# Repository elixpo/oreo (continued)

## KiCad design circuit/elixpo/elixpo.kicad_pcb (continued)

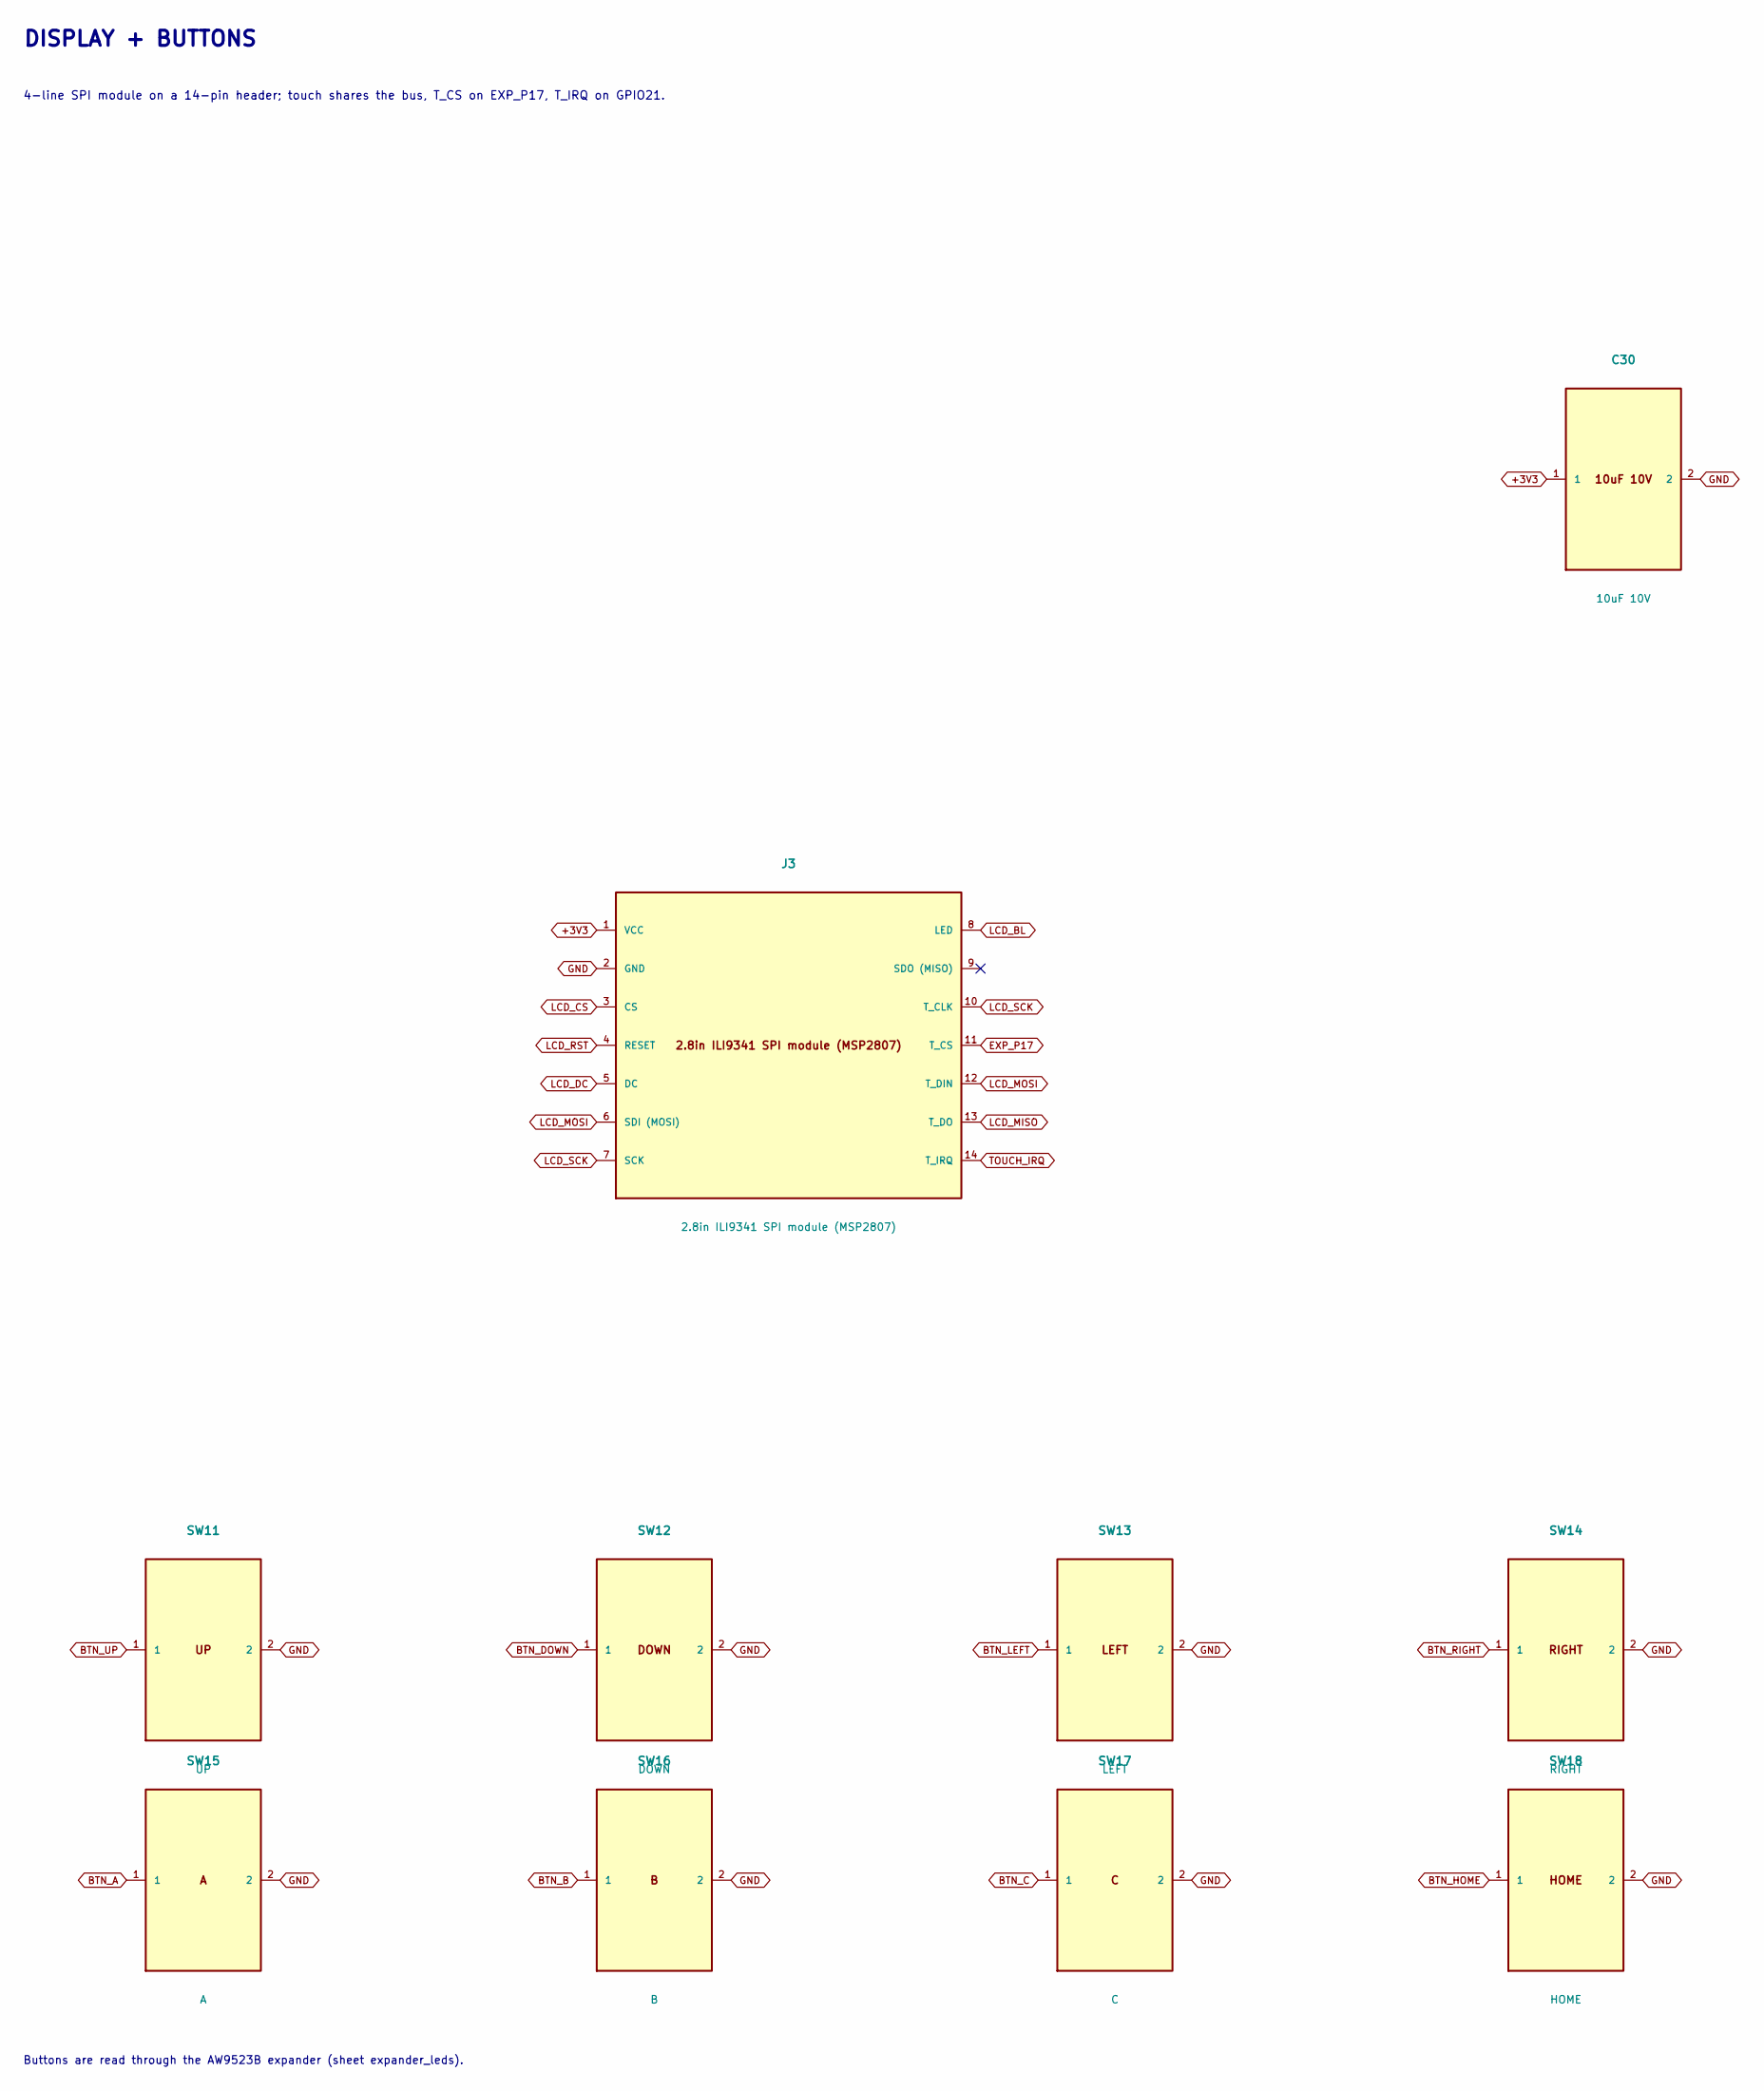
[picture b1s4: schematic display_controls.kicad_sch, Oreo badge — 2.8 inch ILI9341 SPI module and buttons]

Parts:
C30: 10uF 10V; C_0805_2012Metric
J3: 2.8in ILI9341 SPI module (MSP2807); PinSocket_1x14_P2.54mm_Vertical
SW11: UP; SW_PUSH_6mm
SW12: DOWN; SW_PUSH_6mm
SW13: LEFT; SW_PUSH_6mm
SW14: RIGHT; SW_PUSH_6mm
SW15: A; SW_PUSH_6mm
SW16: B; SW_PUSH_6mm
SW17: C; SW_PUSH_6mm
SW18: HOME; SW_PUSH_6mm

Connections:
BTN_A: SW15.1; also elsewhere on the board
BTN_B: SW16.1; also elsewhere on the board
BTN_C: SW17.1; also elsewhere on the board
BTN_DOWN: SW12.1; also elsewhere on the board
BTN_HOME: SW18.1; also elsewhere on the board
BTN_LEFT: SW13.1; also elsewhere on the board
BTN_RIGHT: SW14.1; also elsewhere on the board
BTN_UP: SW11.1; also elsewhere on the board
EXP_P17: J3.11 (T_CS); also elsewhere on the board
GND: C30.2, J3.2 (GND), SW11.2, SW12.2, SW13.2, SW14.2, SW15.2, SW16.2, SW17.2, SW18.2; also elsewhere on the board
LCD_5V: C30.1, J3.1 (VCC); also elsewhere on the board
LCD_BL: J3.8 (LED); also elsewhere on the board
LCD_CS: J3.3 (CS); also elsewhere on the board
LCD_DC: J3.5 (DC); also elsewhere on the board
LCD_MISO: J3.13 (T_DO); also elsewhere on the board
LCD_MOSI: J3.6 (SDI (MOSI)), J3.12 (T_DIN); also elsewhere on the board
LCD_RST: J3.4 (RESET); also elsewhere on the board
LCD_SCK: J3.7 (SCK), J3.10 (T_CLK); also elsewhere on the board
TOUCH_IRQ: J3.14 (T_IRQ); also elsewhere on the board

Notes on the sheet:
DISPLAY + BUTTONS
4-line SPI module on a 14-pin header; touch shares the bus, T_CS on EXP_P17, T_IRQ on GPIO21.
Buttons are read through the AW9523B expander (sheet expander_leds).

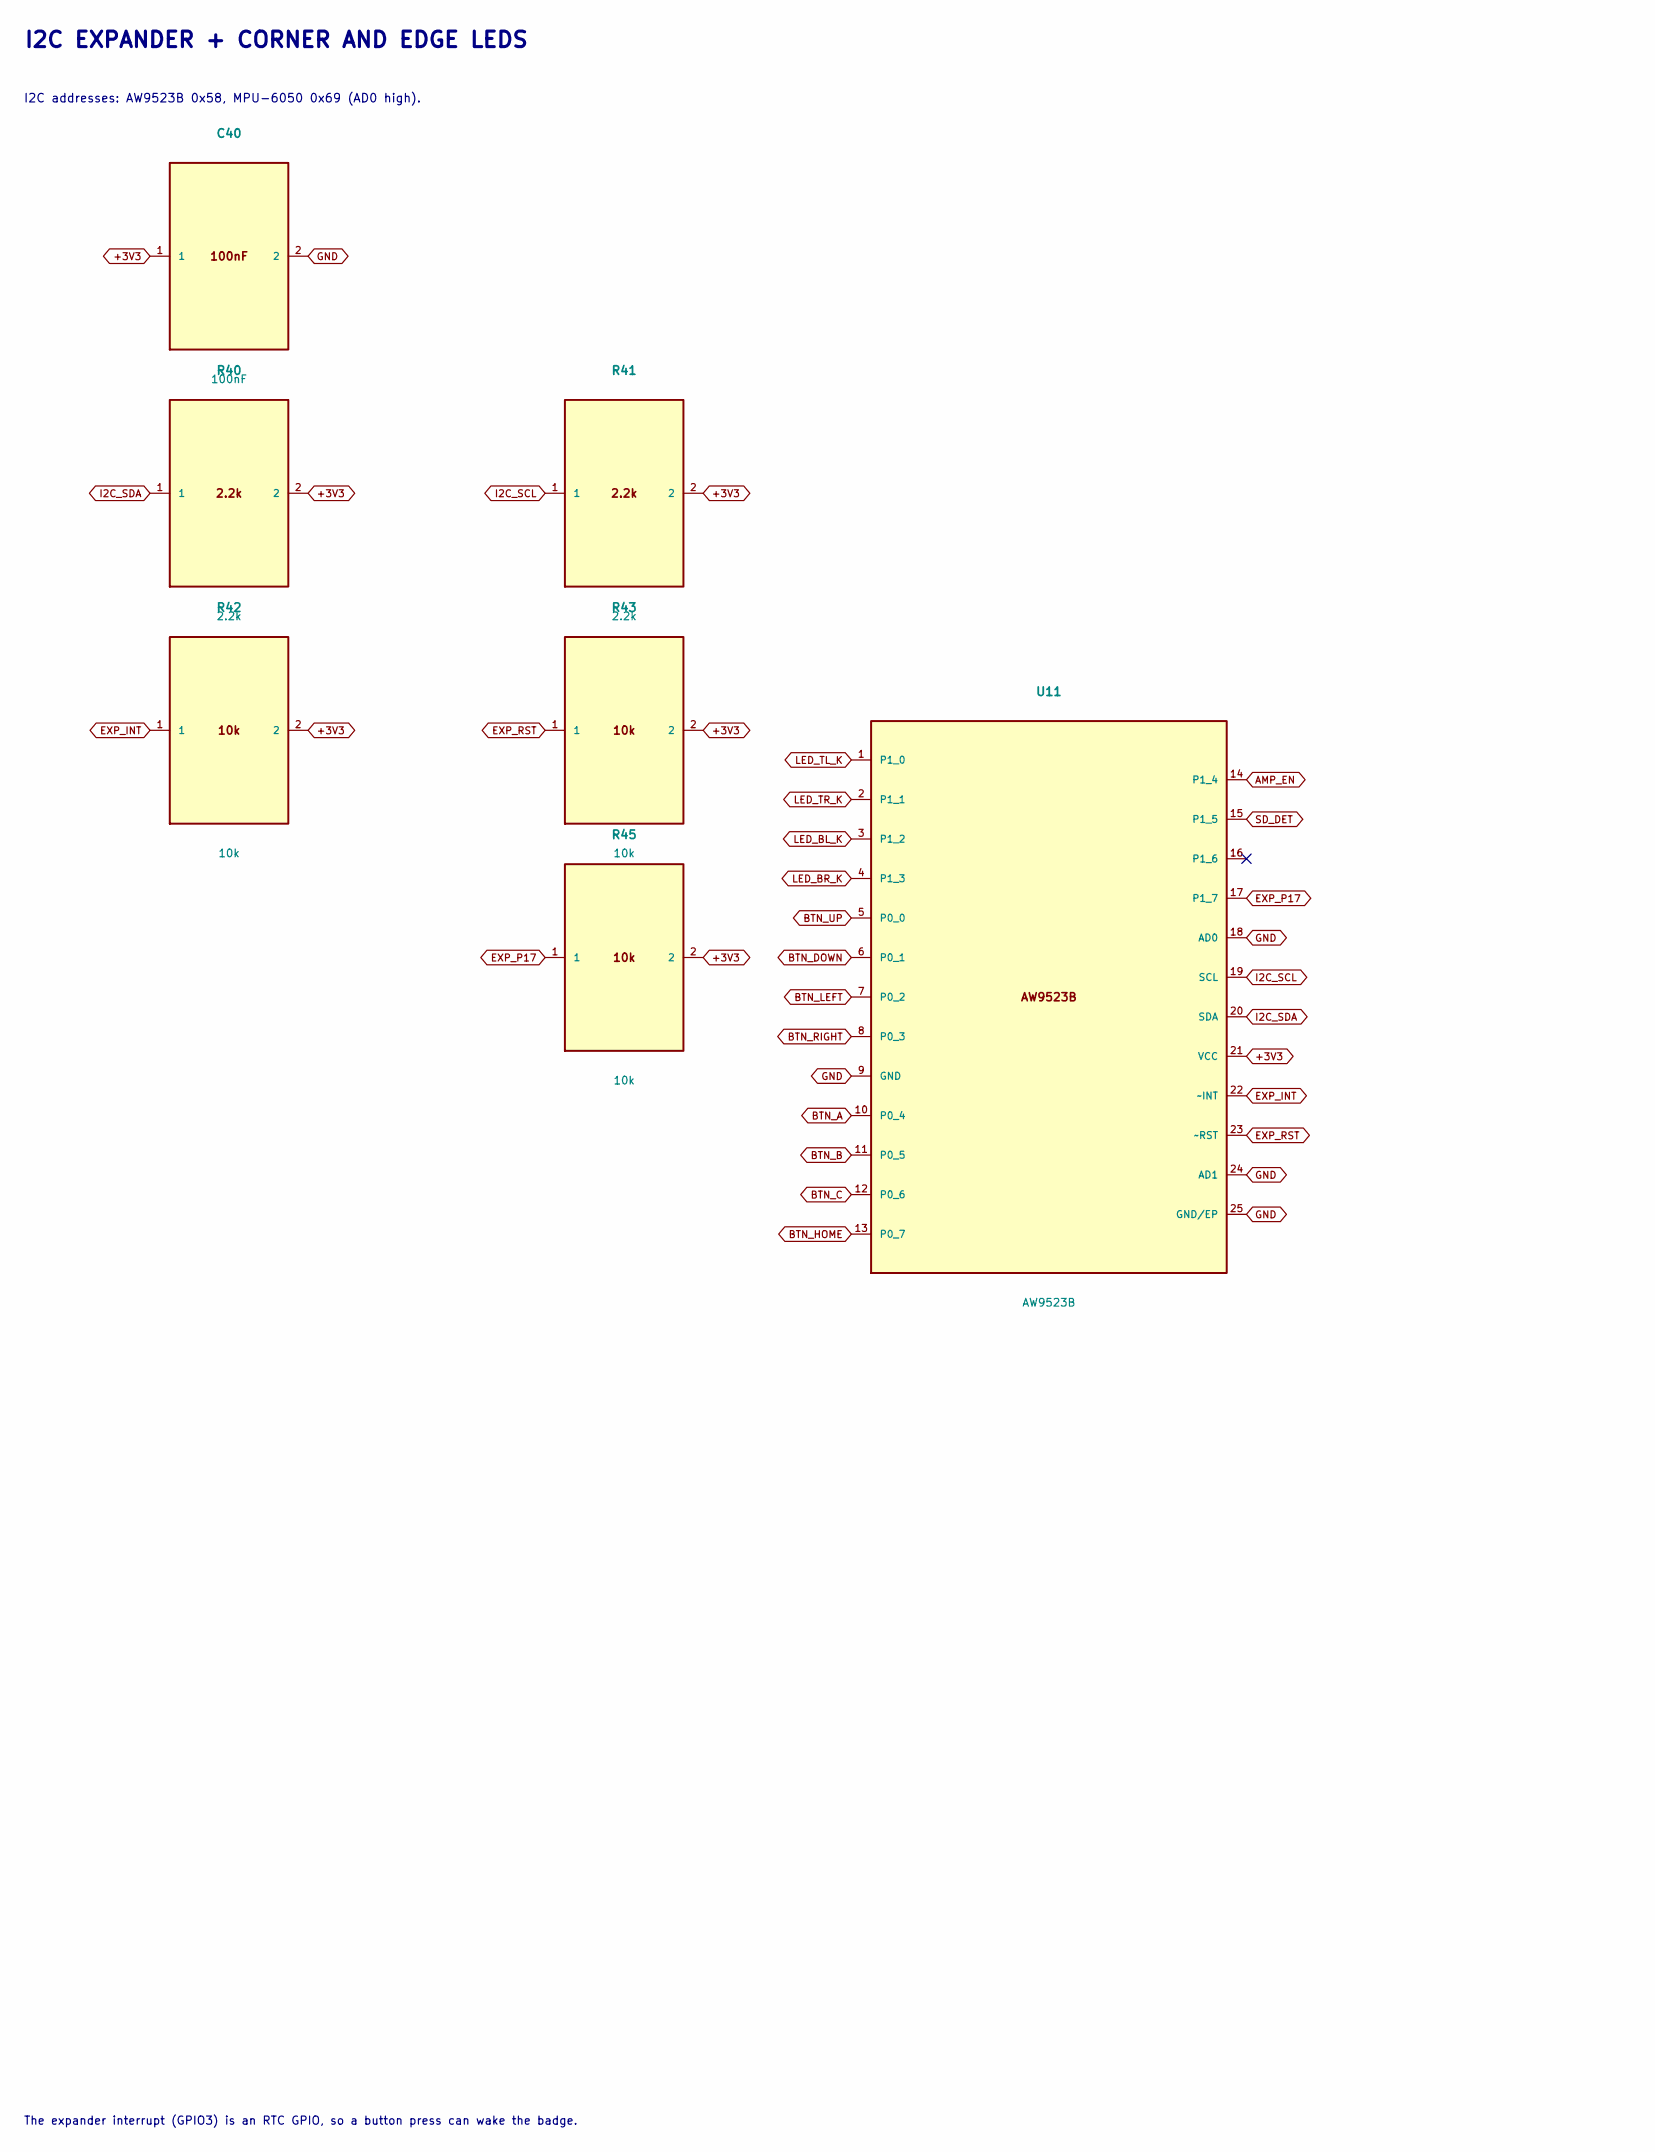
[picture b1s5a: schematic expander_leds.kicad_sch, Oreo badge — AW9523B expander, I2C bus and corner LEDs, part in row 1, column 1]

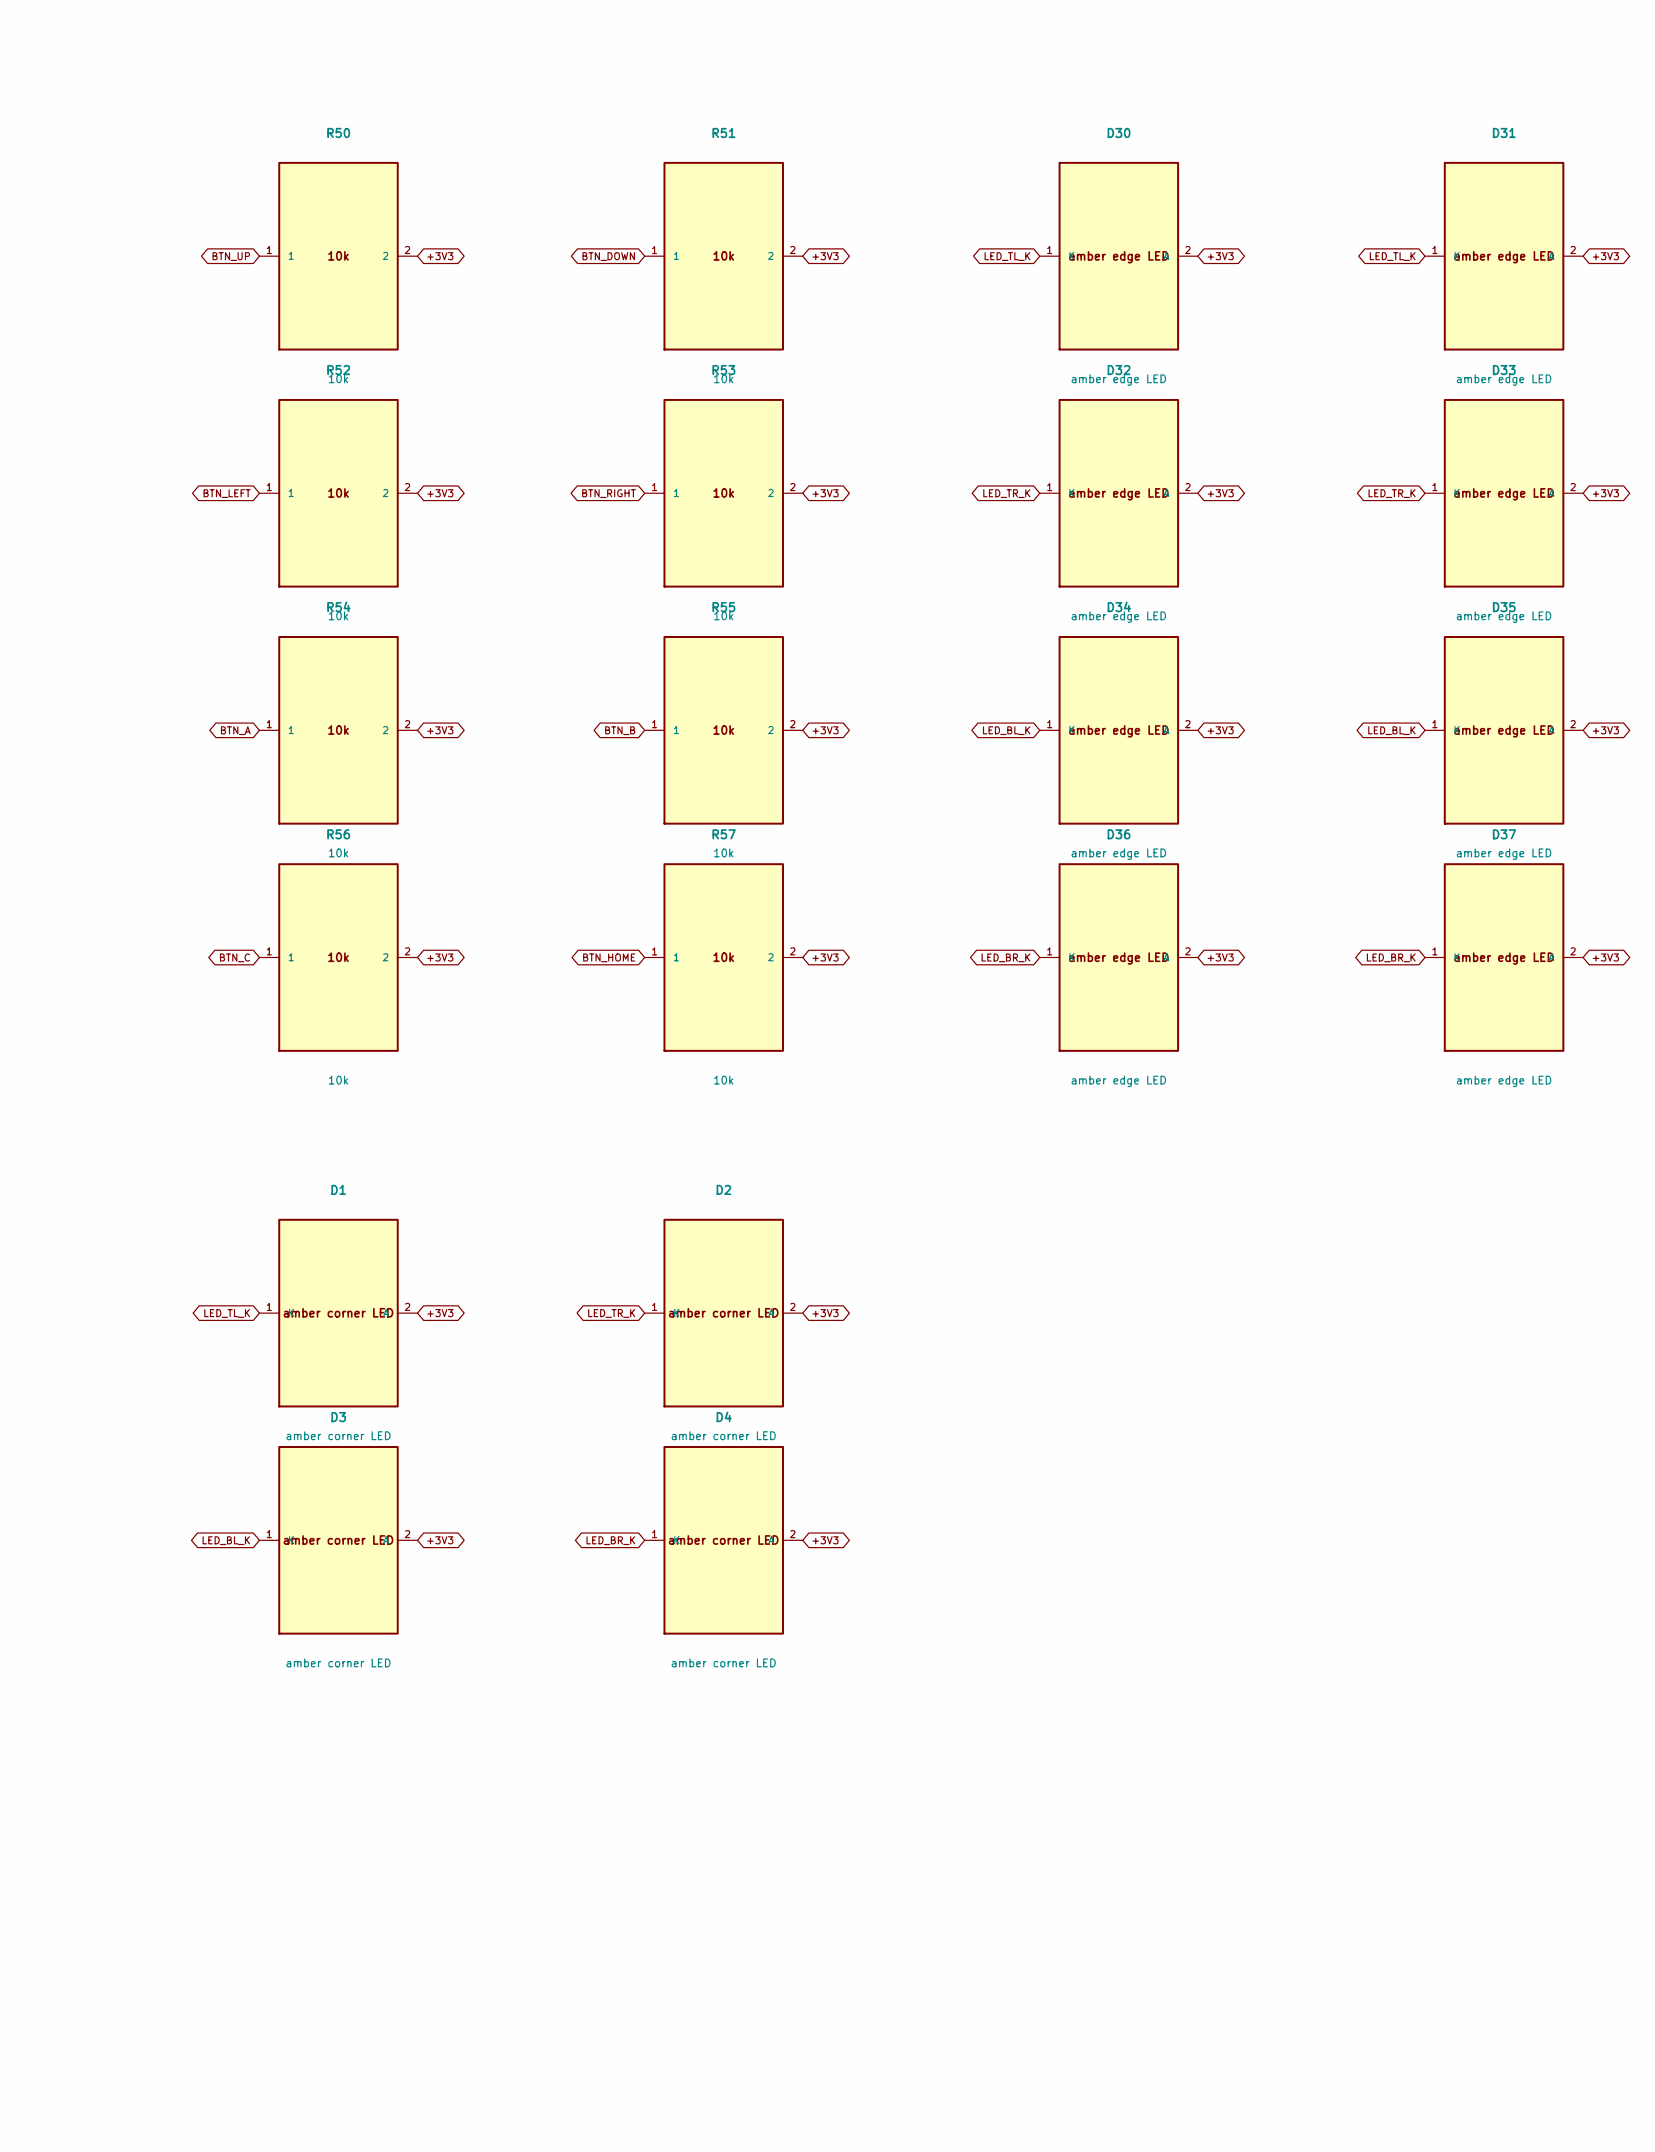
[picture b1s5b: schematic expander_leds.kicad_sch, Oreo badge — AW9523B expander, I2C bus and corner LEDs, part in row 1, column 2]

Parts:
C40: 100nF; C_0402_1005Metric
D1, D2, D3, D4: amber corner LED; LED_0603_1608Metric
D30, D31, D32, D33, D34, D35, D36, D37: amber edge LED; LED_0603_1608Metric
R40, R41: 2.2k; R_0402_1005Metric
R42, R43, R45, R50, R51, R52, R53, R54, R55, R56, R57: 10k; R_0402_1005Metric
U11: AW9523B; QFN-24-1EP_4x4mm_P0.5mm_EP2.7x2.7mm

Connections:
AMP_EN: U11.14 (P1_4); also elsewhere on the board
AUX_ON_N: U11.16 (P1_6); also elsewhere on the board
BTN_A: R54.1, U11.10 (P0_4); also elsewhere on the board
BTN_B: R55.1, U11.11 (P0_5); also elsewhere on the board
BTN_C: R56.1, U11.12 (P0_6); also elsewhere on the board
BTN_DOWN: R51.1, U11.6 (P0_1); also elsewhere on the board
BTN_HOME: R57.1, U11.13 (P0_7); also elsewhere on the board
BTN_LEFT: R52.1, U11.7 (P0_2); also elsewhere on the board
BTN_RIGHT: R53.1, U11.8 (P0_3); also elsewhere on the board
BTN_UP: R50.1, U11.5 (P0_0); also elsewhere on the board
EXP_INT: R42.1, U11.22 (~INT); also elsewhere on the board
EXP_P17: R45.1, U11.17 (P1_7); also elsewhere on the board
EXP_RST: R43.1, U11.23 (~RST)
GND: C40.2, U11.9 (GND), U11.18 (AD0), U11.24 (AD1), U11.25 (GND/EP); also elsewhere on the board
I2C_SCL: R41.1, U11.19 (SCL); also elsewhere on the board
I2C_SDA: R40.1, U11.20 (SDA); also elsewhere on the board
LED_BL_K: D3.1 (K), D34.1 (K), D35.1 (K), U11.3 (P1_2)
LED_BR_K: D4.1 (K), D36.1 (K), D37.1 (K), U11.4 (P1_3)
LED_TL_K: D1.1 (K), D30.1 (K), D31.1 (K), U11.1 (P1_0)
LED_TR_K: D2.1 (K), D32.1 (K), D33.1 (K), U11.2 (P1_1)
SD_DET: U11.15 (P1_5); also elsewhere on the board

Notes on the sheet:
I2C EXPANDER + CORNER AND EDGE LEDS
I2C addresses: AW9523B 0x58, MPU-6050 0x69 (AD0 high).
The expander interrupt (GPIO3) is an RTC GPIO, so a button press can wake the badge.

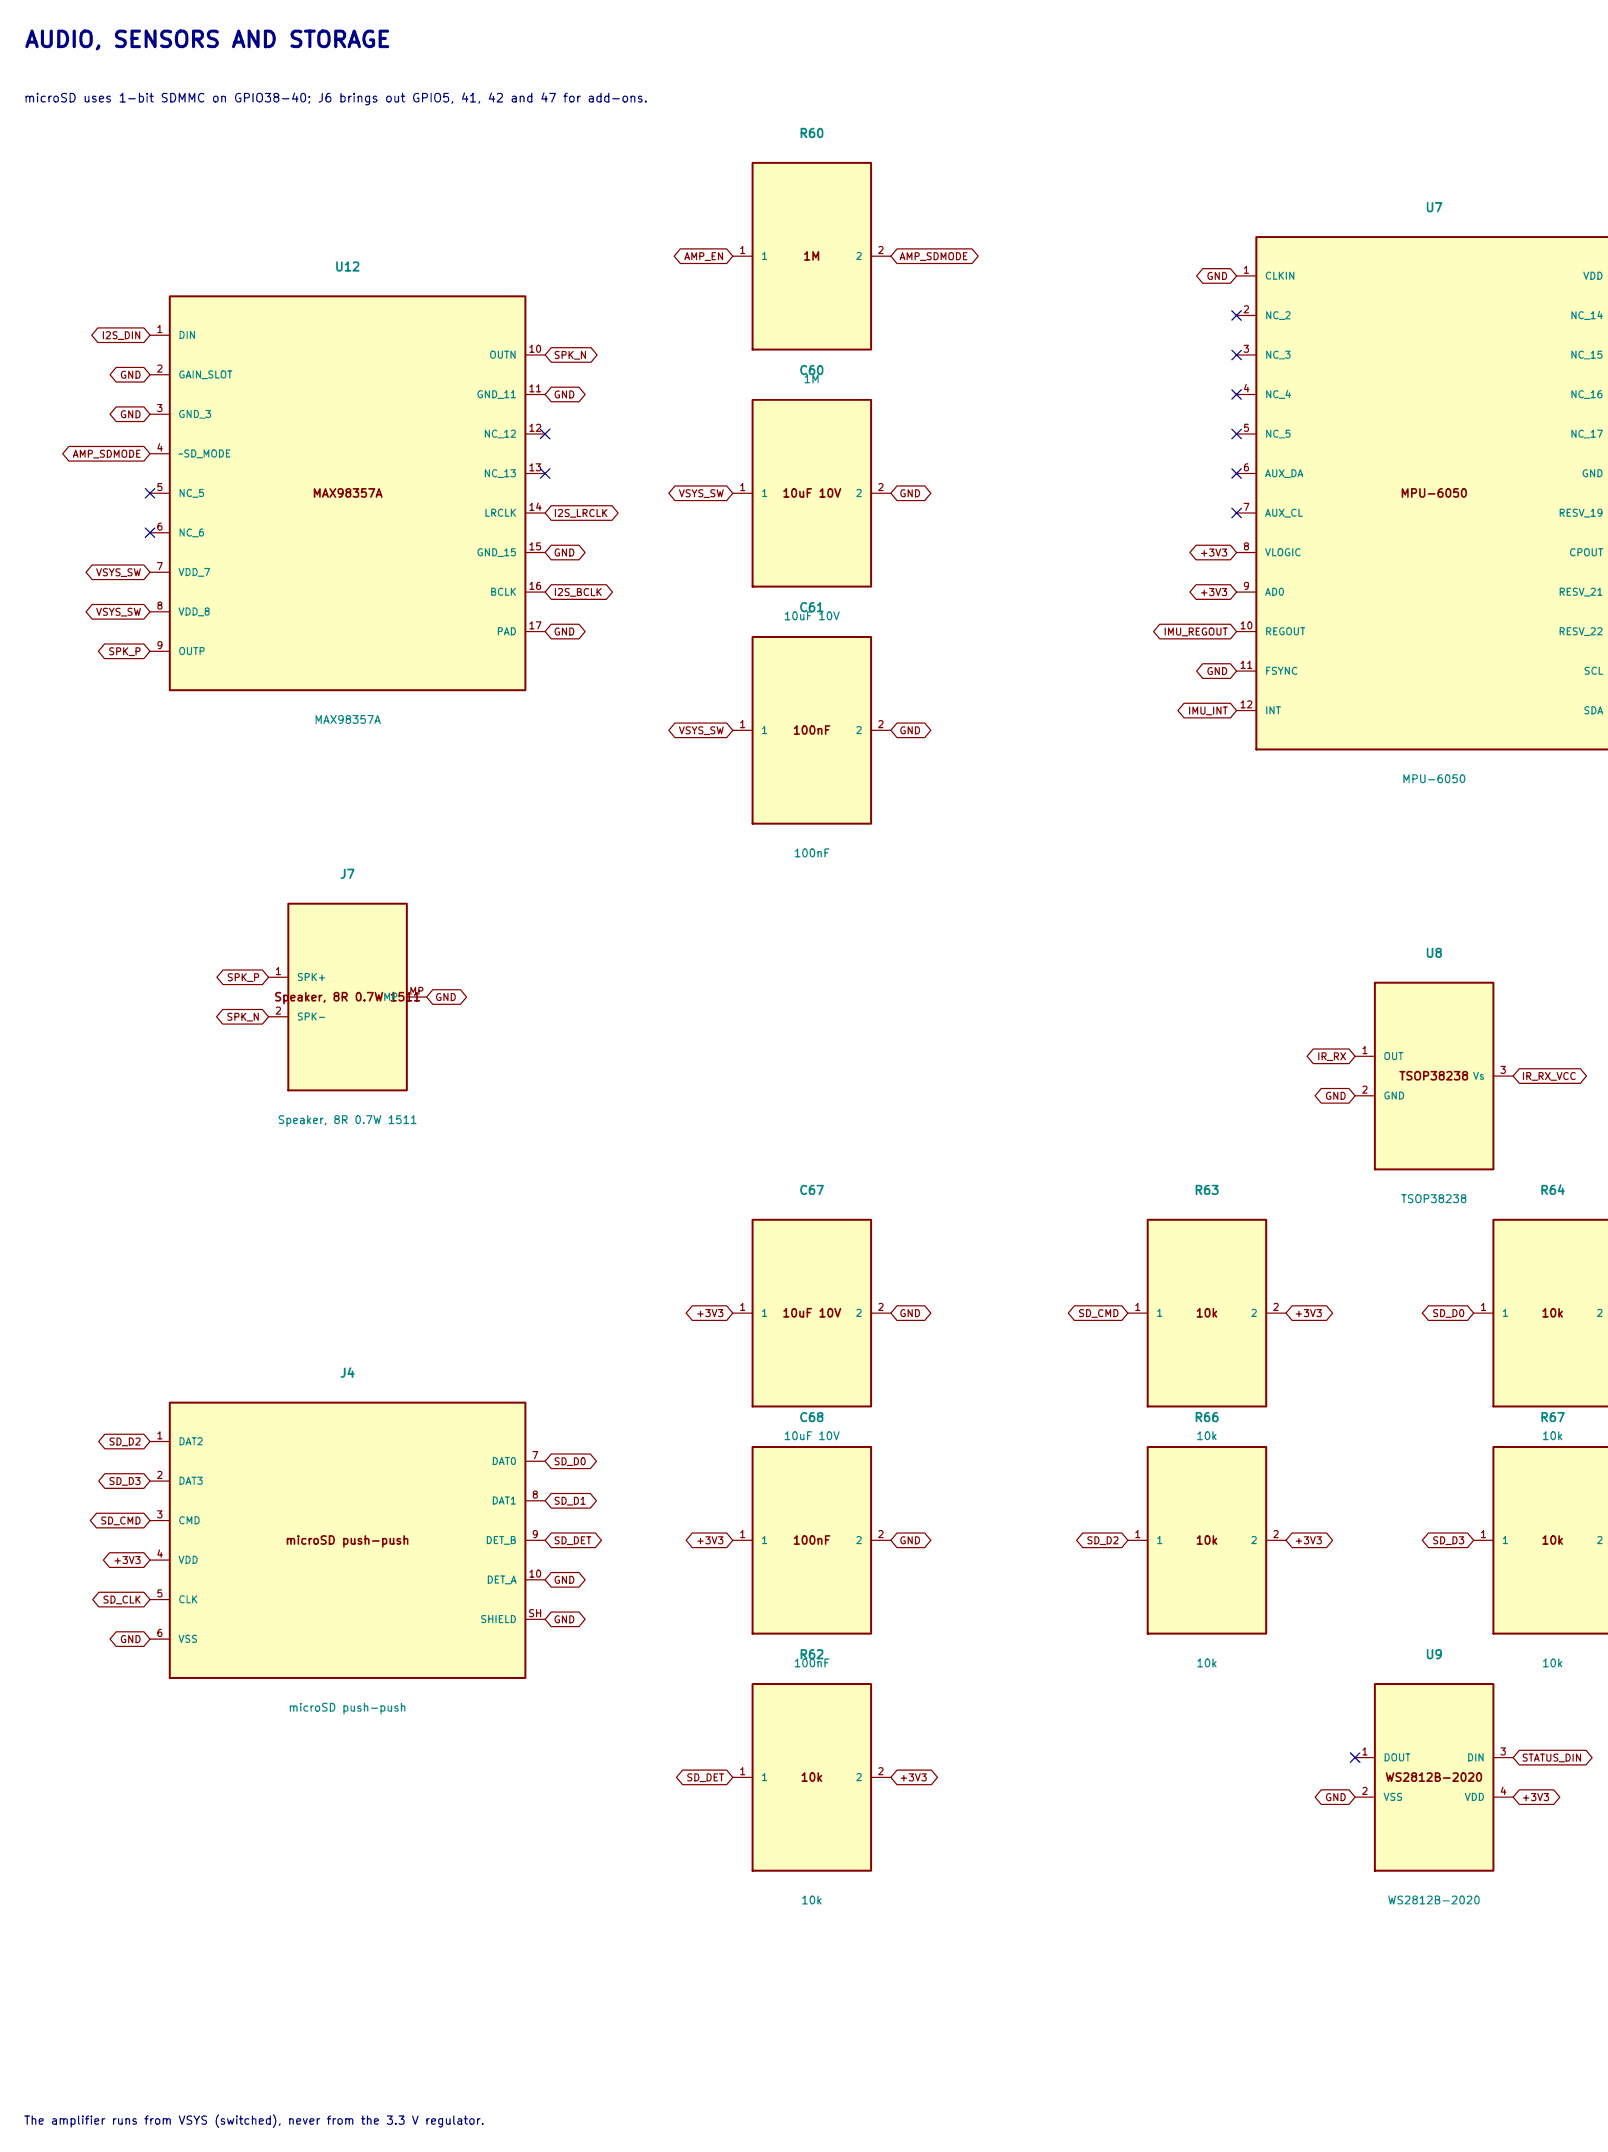
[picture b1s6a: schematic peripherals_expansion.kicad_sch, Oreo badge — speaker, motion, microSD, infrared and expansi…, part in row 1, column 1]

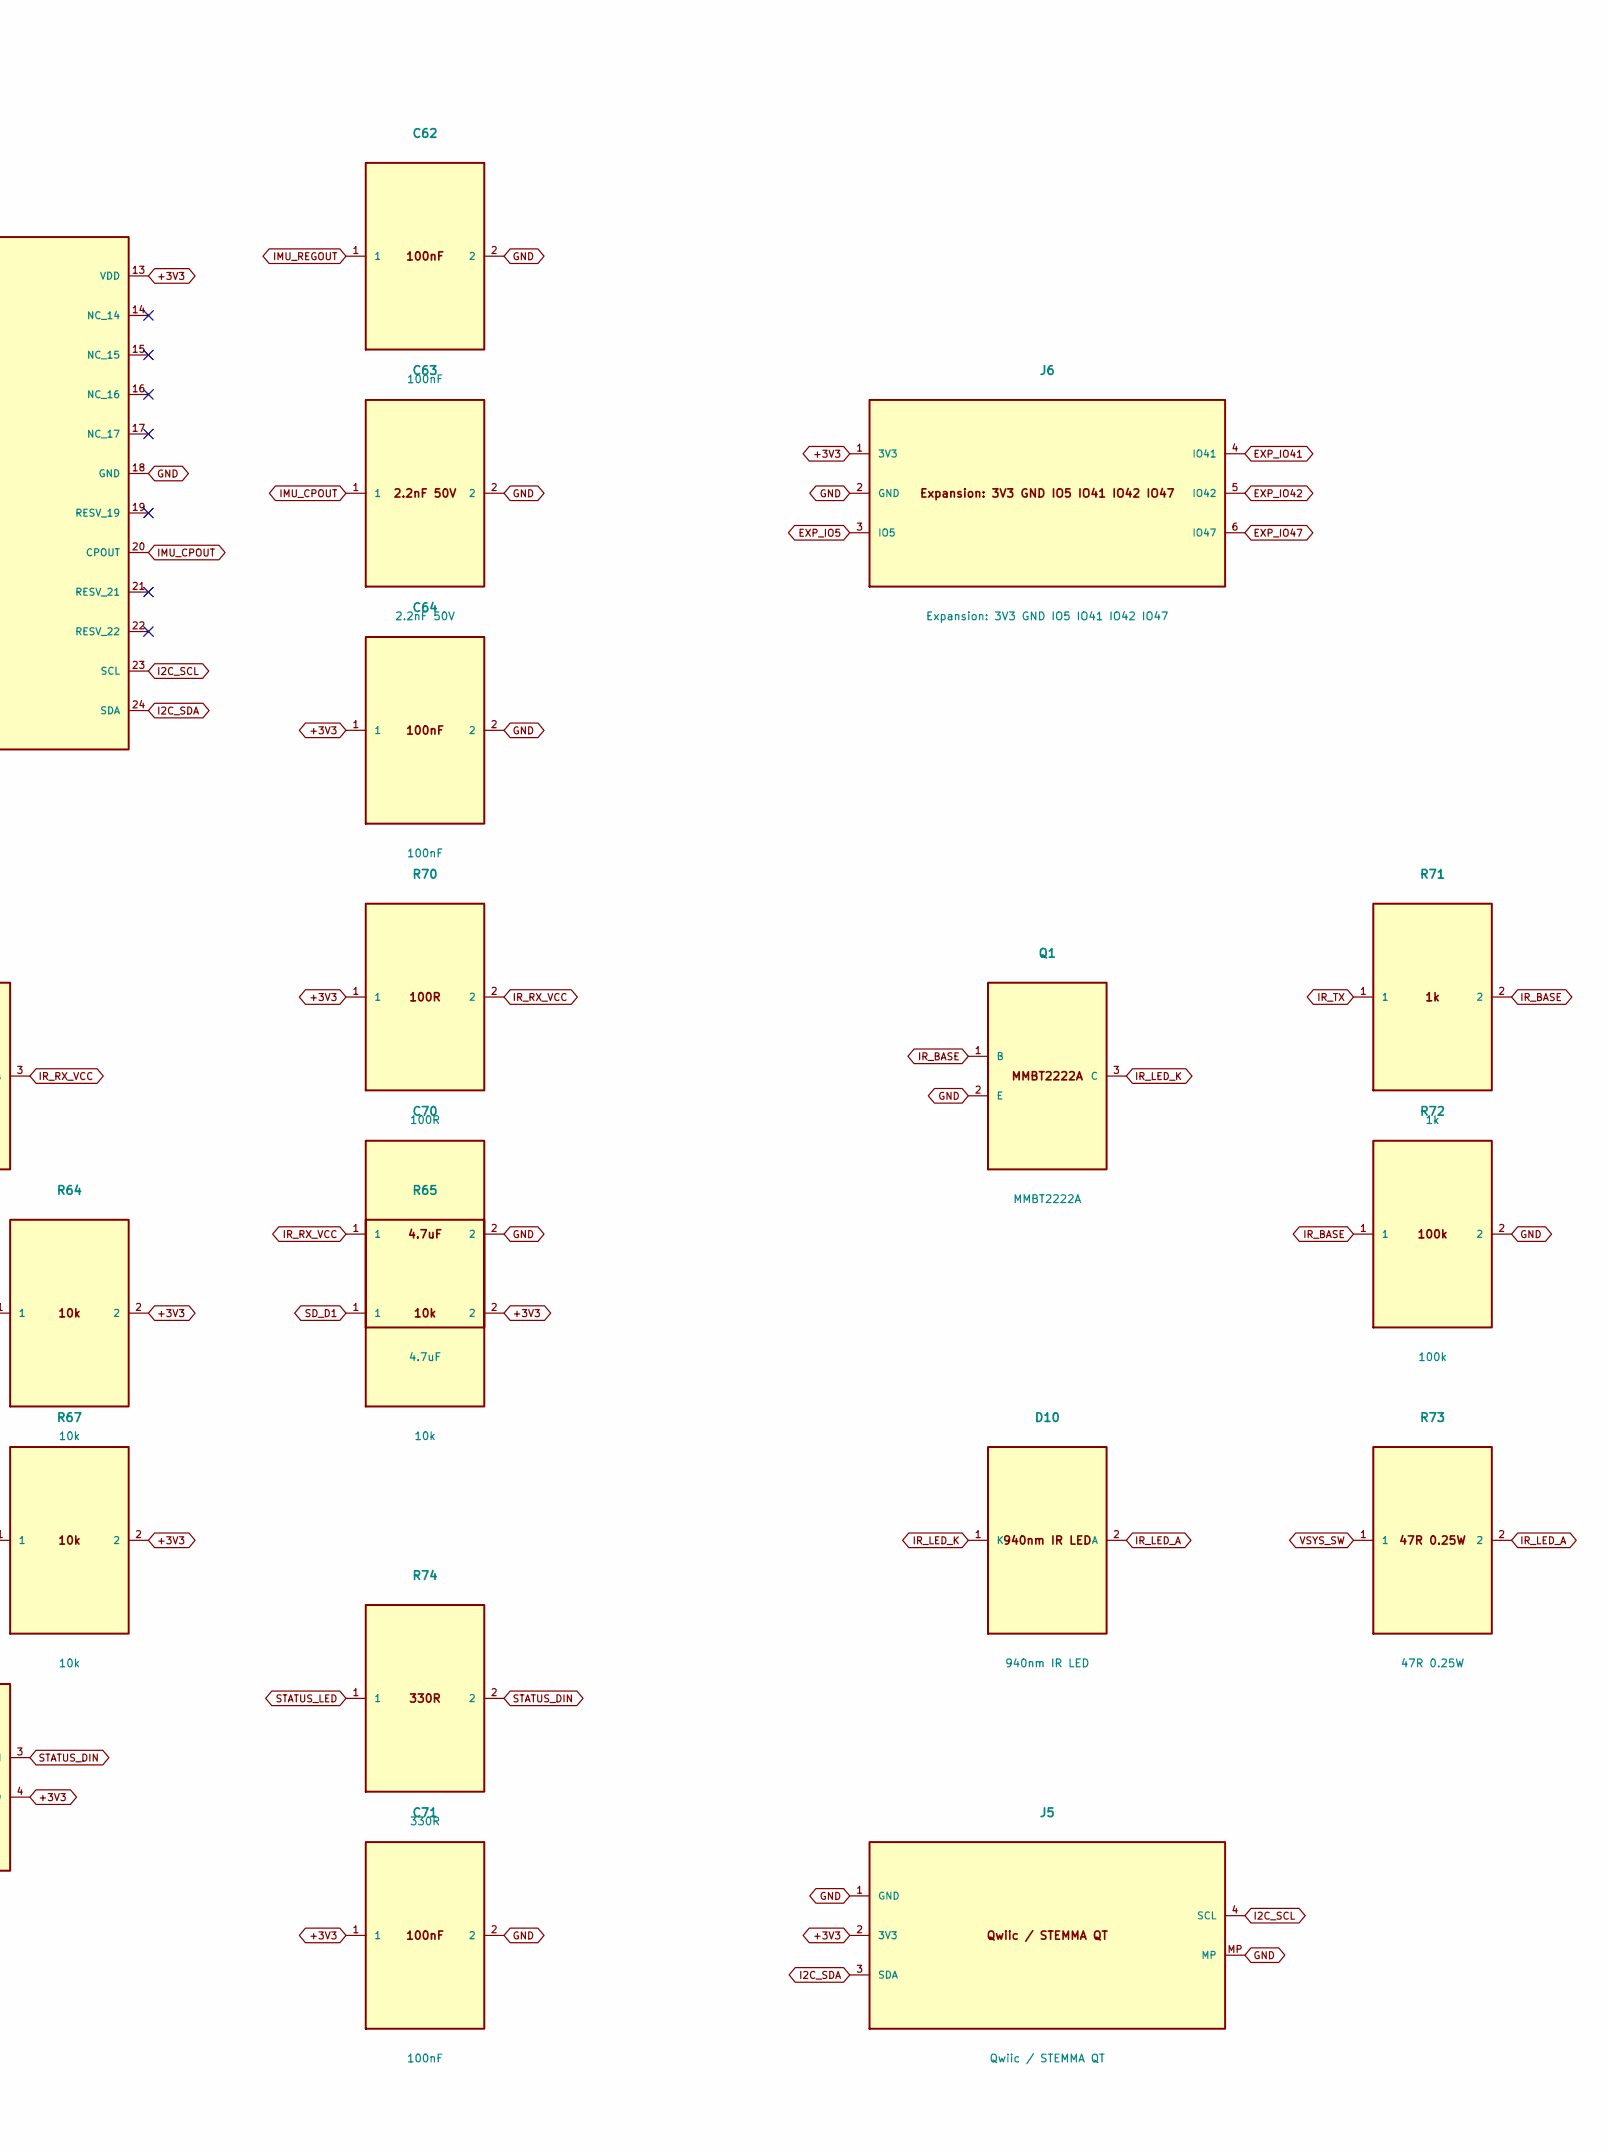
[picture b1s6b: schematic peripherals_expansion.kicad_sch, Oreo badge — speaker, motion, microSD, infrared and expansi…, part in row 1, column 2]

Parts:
C60, C67: 10uF 10V; C_0805_2012Metric
C61, C62, C64, C68, C71: 100nF; C_0402_1005Metric
C63: 2.2nF 50V; C_0402_1005Metric
C70: 4.7uF; C_0603_1608Metric
D10: 940nm IR LED; LED_1206_3216Metric
J4: microSD push-push; microSD_HC_Hirose_DM3AT-SF-PEJM5
J5: Qwiic / STEMMA QT; JST_SH_SM04B-SRSS-TB_1x04-1MP_P1.00mm_Horizontal
J6: Expansion: 3V3 GND IO5 IO41 IO42 IO47; PinHeader_1x06_P2.54mm_Vertical
J7: Speaker, 8R 0.7W 1511; JST_SH_SM02B-SRSS-TB_1x02-1MP_P1.00mm_Horizontal
Q1: MMBT2222A; SOT-23
R60: 1M; R_0402_1005Metric
R62, R63, R64, R65, R66, R67: 10k; R_0402_1005Metric
R70: 100R; R_0402_1005Metric
R71: 1k; R_0402_1005Metric
R72: 100k; R_0402_1005Metric
R73: 47R 0.25W; R_0805_2012Metric
R74: 330R; R_0402_1005Metric
U7: MPU-6050; InvenSense_QFN-24_4x4mm_P0.5mm
U8: TSOP38238; Vishay_MINICAST-3Pin
U9: WS2812B-2020; LED_WS2812B-2020_PLCC4_2.0x2.0mm
U12: MAX98357A; TQFN-16-1EP_3x3mm_P0.5mm_EP1.23x1.23mm

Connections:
AMP_EN: R60.1; also elsewhere on the board
AMP_SDMODE: R60.2, U12.4 (~SD_MODE)
GND: C60.2, C61.2, C62.2, C63.2, C64.2, C67.2, C68.2, C70.2, C71.2, J4.6 (VSS), J4.10 (DET_A), J4.SH (SHIELD), J5.1 (GND), J5.MP, J6.2 (GND), J7.MP, Q1.2 (E), R72.2, U7.1 (CLKIN), U7.11 (FSYNC), U7.18 (GND), U8.2 (GND), U9.2 (VSS), U12.2 (GAIN_SLOT), U12.3 (GND_3), U12.11 (GND_11), U12.15 (GND_15), U12.17 (PAD); also elsewhere on the board
I2C_SCL: J5.4 (SCL), U7.23 (SCL); also elsewhere on the board
I2C_SDA: J5.3 (SDA), U7.24 (SDA); also elsewhere on the board
I2S_BCLK: U12.16 (BCLK); also elsewhere on the board
I2S_DIN: U12.1 (DIN); also elsewhere on the board
I2S_LRCLK: U12.14 (LRCLK); also elsewhere on the board
IMU_CPOUT: C63.1, U7.20 (CPOUT)
IMU_INT: U7.12 (INT); also elsewhere on the board
IMU_REGOUT: C62.1, U7.10 (REGOUT)
IR_BASE: Q1.1 (B), R71.2, R72.1
IR_LED_A: D10.2 (A), R73.2
IR_LED_K: D10.1 (K), Q1.3 (C)
IR_RX: U8.1 (OUT); also elsewhere on the board
IR_RX_VCC: C70.1, R70.2, U8.3 (Vs)
IR_TX: R71.1; also elsewhere on the board
SD_CLK: J4.5 (CLK); also elsewhere on the board
SD_CMD: J4.3 (CMD), R63.1; also elsewhere on the board
SD_D0: J4.7 (DAT0), R64.1; also elsewhere on the board
SD_D1: J4.8 (DAT1), R65.1
SD_D2: J4.1 (DAT2), R66.1
SD_D3: J4.2 (DAT3), R67.1
SD_DET: J4.9 (DET_B), R62.1; also elsewhere on the board
SPK_N: J7.2 (SPK-), U12.10 (OUTN)
SPK_P: J7.1 (SPK+), U12.9 (OUTP)
STATUS_DIN: R74.2, U9.3 (DIN)
STATUS_LED: R74.1; also elsewhere on the board
VSYS_SW: C60.1, C61.1, R73.1, U12.7 (VDD_7), U12.8 (VDD_8); also elsewhere on the board

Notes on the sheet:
AUDIO, SENSORS AND STORAGE
microSD uses 1-bit SDMMC on GPIO38-40; J6 brings out GPIO5, 41, 42 and 47 for add-ons.
The amplifier runs from VSYS (switched), never from the 3.3 V regulator.

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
